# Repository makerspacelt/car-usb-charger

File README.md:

car-usb-charger
===============

USB devices charger for use in car

Simply put, it's a buck converter from 12-24V car voltage to 5V needed by
USB devices. Intention was to pack as much current as possible in a
relatively small form factor. Device can produce about 2A continuously on a
5V output, mostly limited by self heating.

## Software used

* Schematics and board was produced with [eagle v6.4](http://www.cadsoftusa.com/eagle-pcb-design-software/product-overview/)
* G-code generated with eagle addon [pcb-gcode v3.6](https://groups.yahoo.com/neo/groups/pcb-gcode/info)

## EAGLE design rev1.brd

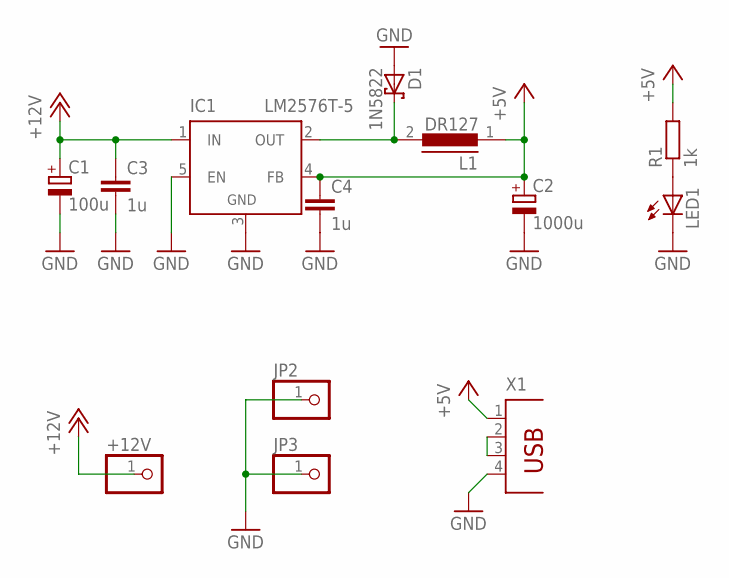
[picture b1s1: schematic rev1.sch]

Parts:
+12V: PINHD-1X1; 1X01
C1: 100u; TT2D6L
C2: 1000u; TT5D9L
C3, C4: 1u; C0805K
D1: 1N5822; DO201_5
IC1: LM2576T-5; TO220-51
JP2, JP3: PINHD-1X1; 1X01
L1: DR127
LED1: LED3MM
R1: 1k; R0805
X1: PN87520

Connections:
+5V: C2.+, C4.1, IC1.4 (FB), L1.1, R1.2, X1.1
+12V: +12V.1, C1.+, C3.1, IC1.1 (IN)
GND: C1.-, C2.-, C3.2, C4.2, D1.P$2 (A), IC1.3 (GND), IC1.5 (EN), JP2.1, JP3.1, LED1.K (C), X1.4
unnamed: LED1.A, R1.1
unnamed: D1.P$1 (C), IC1.2 (OUT), L1.2
unnamed: X1.2, X1.3

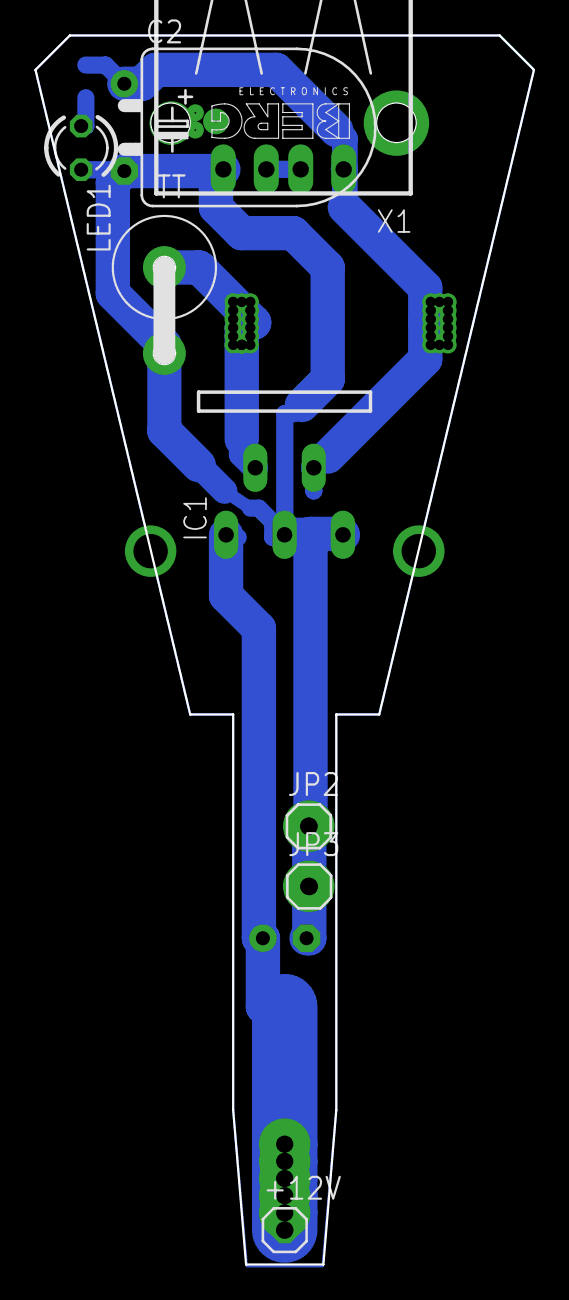
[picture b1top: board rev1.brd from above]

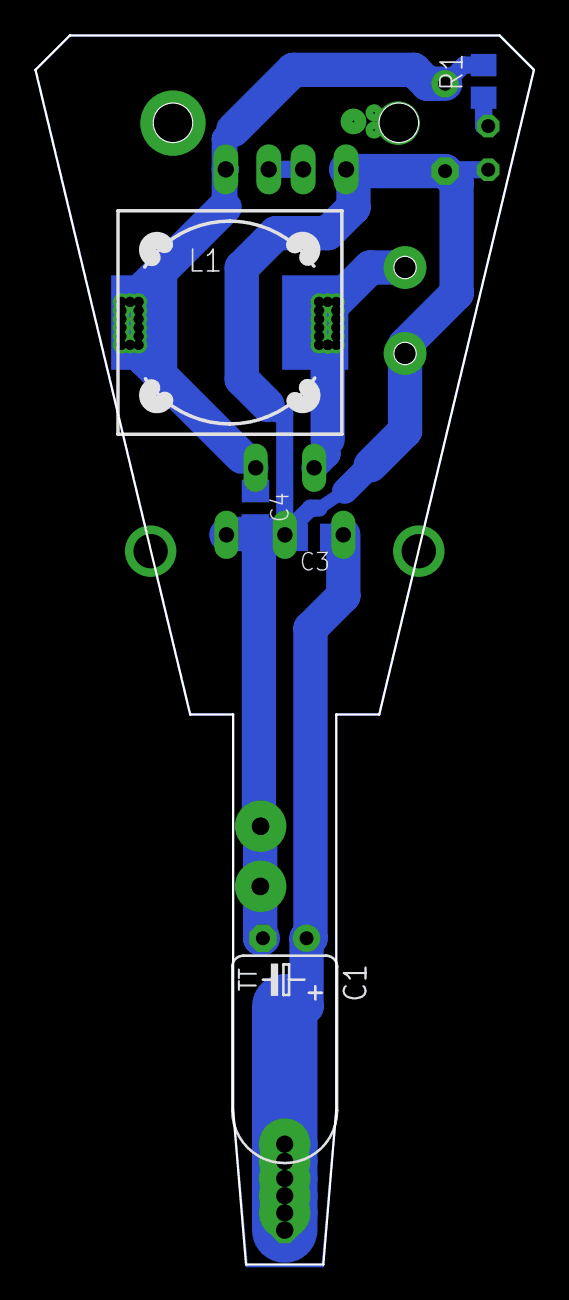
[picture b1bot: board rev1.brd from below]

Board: 2 copper layers, 29.0 x 71.5 mm, 13 parts (5 on the bottom side), 6 nets.

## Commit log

2014-04-19 adding first version of project
2014-04-19 updating readme file to be somewhat useful
